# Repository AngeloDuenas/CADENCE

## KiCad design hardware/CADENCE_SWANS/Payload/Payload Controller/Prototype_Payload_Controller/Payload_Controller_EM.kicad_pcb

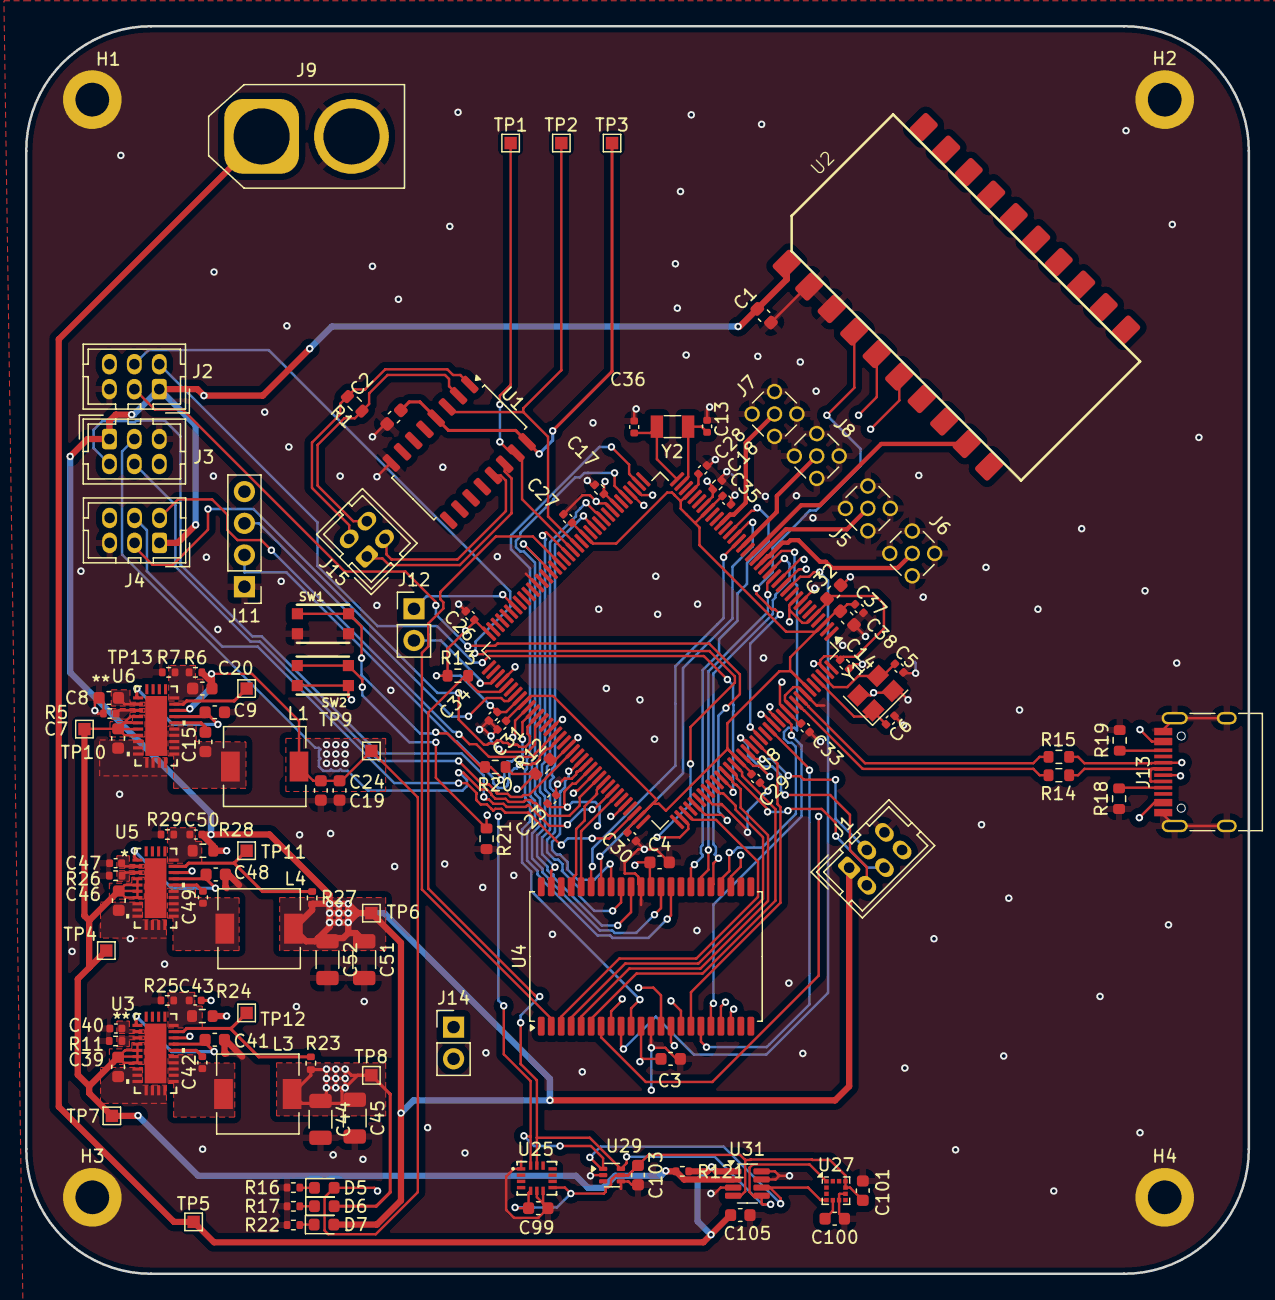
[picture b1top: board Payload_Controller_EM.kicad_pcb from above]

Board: 4 copper layers, 98.0 x 100.0 mm, 126 parts (0 on the bottom side), 110 nets.

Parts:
C1, C2, C3, C4: 10uF; C_0603_1608Metric
C5, C6: 12pF; C_0402_1005Metric
C7, C32, C39, C46: 4.7uF; C_0603_1608Metric
C8: 10nF; C_0603_1608Metric
C9, C38, C41, C48: 1uF; C_0603_1608Metric
C13, C36: 17pF; C_0402_1005Metric
C14, C17, C18: 100nF; R_0402_1005Metric
C15, C101, C103, C105: 100nF; C_0603_1608Metric
C19, C24: 47uF; C_0603_1608Metric
C20: 4.7pF; C_0603_1608Metric
C23, C26, C27, C28, C29, C30, C31, C33, C34, C35, C37, C42, C49: 100nF; C_0402_1005Metric
C40, C47: 10nF; C_0402_1005Metric
C43, C50: 10pF; C_0402_1005Metric
C44, C45, C51, C52: 47uF; C_1206_3216Metric
C99: 10u; C_0603_1608Metric
C100: 220nF; C_0603_1608Metric
D5, D6, D7: RED; LED_0603_1608Metric
H1, H2, H3, H4: MountingHole_Pad_M2.5_2.7mm; MountingHole_2.7mm_M2.5_DIN965_Pad
J1, J2, J3, J4: Conn_01x06_Pin; Hirose_DF11-6DP-2DSA_2x03_P2.00mm_Vertical
J5, J6, J7, J8: Conn_Coaxial; MMCX_Molex_73415-1471_Vertical
J9: Conn_01x02; AMASS_XT60-F_1x02_P7.20mm_Vertical
J11: Conn_01x04; PinHeader_1x04_P2.54mm_Vertical
J12, J14: Conn_01x02; PinHeader_1x02_P2.54mm_Vertical
J13: USB_C_Receptacle_USB2.0_16P; USB_C_Receptacle_HRO_TYPE-C-31-M-12
J15: Conn_02x02_Top_Bottom; Hirose_DF11-4DP-2DSA_2x02_P2.00mm_Vertical
L1: 1.8uH; L_6.3x6.3_H3
L3: 2.5uH; L_6.3x6.3_H3
L4: 10uH; L_6.3x6.3_H3
R1: 120; R_0603_1608Metric
R5, R11: 18.2k; R_0402_1005Metric
R6: 1M; R_0402_1005Metric
R7: 412k; R_0402_1005Metric
R12, R13: 4.7k; R_0603_1608Metric
R14, R15: 22; R_0603_1608Metric
R16, R17, R22: 330; R_0402_1005Metric
R18, R19: 5.1k; R_0603_1608Metric
R20, R21: 10k; R_0603_1608Metric
R23, R27: 100k; R_0402_1005Metric
R24, R28: 1M; R_0603_1608Metric
R25: 243k; R_0402_1005Metric
R26: 41.2k; R_0402_1005Metric
R29: 88.7k; R_0402_1005Metric
R121: 0.002; R_0402_1005Metric
SW1, SW2: KMR2; BTN_KMR2_4.6X2.8
TP1, TP2, TP3, TP4, TP5, TP6, TP7, TP8, TP9, TP10, TP11, TP12, TP13: TestPoint; TestPoint_Pad_1.0x1.0mm
U1: SN65C1168ERGYR; SOP-16_4.55x10.3mm_P1.27mm
U2: RM-VT01-A
U3, U5, U6: LT8612; QFN-28_UDE_LTI
U4: TSOP-II-44_10.16x18.41mm_P0.8mm
U8: ATSAMV71Q21B-A; LQFP-144_20x20mm_P0.5mm
U25: LSM6DSO; LGA-14_L3.0-W2.5-P0.50-TL
U27: LIS2MDL; LGA-12_2x2mm_P0.5mm
U29: TMP112xxDRL; SOT-563
U31: INA219AxDCN; SOT-23-8
Y1: ABM3B-12.000MHZ-B2-T; Crystal_SMD_3225-4Pin_3.2x2.5mm
Y2: ABS07-32.768KHZ-T; Crystal_SMD_3215-2Pin_3.2x1.5mm

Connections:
3V3 Power Good: TP13.1, U6.23 (PG)
5V Power Good: R23.2, TP12.1, U3.23 (PG)
12V Power Good: R27.2, TP11.1, U5.23 (PG)
+1V2: C27.1, C28.1, C29.1, C30.1, C31.1, C35.1, C37.1, C38.1, U8.3 (VDDOUT), U8.29 (VDDCORE), U8.33 (VDDCORE), U8.50 (VDDCORE), U8.81 (VDDCORE), U8.107 (VDDCORE), U8.123 (VDDPLL), U8.139 (VDDUTMIC)
+3.3V: C19.1, C20.2, C24.1, C99.1, C101.1, C103.1, D5.2 (A), L1.2, R6.2, TP9.1, U6.22 (BIAS), U25.5 (VDDIO), U25.8 (VDD), U27.9 (Vdd), U27.10 (Vdd_IO), U29.5 (V+), U31.4 (VS)
+3V3: C3.1, C4.1, C14.1, C17.1, C18.1, C23.1, C26.1, C32.1, C33.1, C34.1, J11.4, J13.A4 (VBUS), J13.A9 (VBUS), J13.B4 (VBUS), J13.B9 (VBUS), J14.2, R12.1, R13.1, R20.1, SW2.A, SW2.A' (P1), U4.11 (VDD), U4.33 (VDD), U8.5 (VDDIN), U8.9 (VREFP), U8.30 (VDDIO), U8.43 (VDDIO), U8.72 (VDDIO), U8.80 (VDDIO), U8.96 (VDDIO), U8.134 (VDDUTMII), U8.143 (VDDPLLUSB)
+5V: C2.1, C43.2, C44.1, C45.1, D6.2 (A), L3.2, R23.1, R24.2, TP3.1, TP8.1, U1.4 (1DE), U1.16 (VCC), U3.22 (BIAS)
+12V: C1.1, C50.2, C51.1, C52.1, D7.2 (A), J1.1, J2.1, J3.1, J4.1, L4.2, R27.1, R28.2, TP6.1, U2.1 (Vdd), U5.22 (BIAS)
/Flight Computer Interface/Payload_RX+: J15.4, R1.1, U1.2 (1A)
/Flight Computer Interface/Payload_RX-: J15.3, R1.2, U1.1 (1B)
/Flight Computer Interface/Payload_TX+: J15.2, U1.13 (1Z)
/Flight Computer Interface/Payload_TX-: J15.1, U1.14 (1Y)
/Instrument/CTRL_EN_0: U2.5 (CTRL_EN), U8.132 (PD1)
/Instrument/CTRL_EN_1: J1.2, U8.126 (PD4)
/Instrument/CTRL_EN_2: J2.2, U8.119 (PD7)
/Instrument/CTRL_EN_3: J3.2, U8.101 (PD10)
/Instrument/CTRL_EN_4: J4.2, U8.88 (PD13)
/Instrument/CTRL_R1_0: U2.6 (CTRL_R1), U8.131 (PD2)
/Instrument/CTRL_R1_1: J1.3, U8.125 (PD5)
/Instrument/CTRL_R1_2: J2.3, U8.113 (PD8)
/Instrument/CTRL_R1_3: J3.3, U8.98 (PD11)
/Instrument/CTRL_R1_4: J4.3, U8.84 (PD14)
/Instrument/CTRL_R2_0: U2.4 (CTRL_R2), U8.128 (PD3)
/Instrument/CTRL_R2_1: J1.4, U8.121 (PD6)
/Instrument/CTRL_R2_2: J2.4, U8.110 (PD9)
/Instrument/CTRL_R2_3: J3.4, U8.92 (PD12)
/Instrument/CTRL_R2_4: J4.4, U8.106 (PD15)
/Instrument/RADFET_OUT0: U2.9 (RADFET_OUT), U8.19 (PC13)
/Instrument/RADFET_OUT1: J5.1 (In), U8.18 (PC15)
/Instrument/RADFET_OUT2: J6.1 (In), U8.17 (PC12)
/Instrument/RADFET_OUT3: J7.1 (In), U8.26 (PB2)
/Instrument/RADFET_OUT4: J8.1 (In), U8.21 (PB0)
/MRAM/A0: U4.3 (A0), U8.111 (PC18)
/MRAM/A1: U4.4 (A1), U8.117 (PC19)
/MRAM/A2: U4.5 (A2), U8.120 (PC20)
/MRAM/A3: U4.6 (A3), U8.122 (PC21)
/MRAM/A4: U4.7 (A4), U8.124 (PC22)
/MRAM/A5: U4.16 (A5), U8.127 (PC23)
/MRAM/A6: U4.17 (A6), U8.130 (PC24)
/MRAM/A7: U4.18 (A7), U8.133 (PC25)
/MRAM/A8: U4.19 (A8), U8.13 (PC26)
/MRAM/A9: U4.20 (A9), U8.12 (PC27)
/MRAM/A10: U4.25 (A10), U8.76 (PC28)
/MRAM/A11: U4.26 (A11), U8.16 (PC29)
/MRAM/A12: U4.27 (A12), U8.15 (PC30)
/MRAM/A13: U4.28 (A13), U8.14 (PC31)
/MRAM/A14: U4.29 (A14), U8.24 (PA18)
/MRAM/A15: U4.38 (A15), U8.23 (PA19)
/MRAM/A16: U4.39 (A16), U8.22 (PA20)
/MRAM/A17: U4.40 (A17), U8.102 (PA0)
/MRAM/A18: U4.41 (A18), U8.99 (PA1)
/MRAM/A19: U4.43 (A19), U8.46 (PA23)
/MRAM/A20: U4.2 (A20), U8.56 (PA24)
/MRAM/MRAM_CTRL.CS: U4.8 (CS), U8.97 (PC14)
/MRAM/MRAM_CTRL.OE: U4.37 (OE), U8.94 (PC11)
/MRAM/MRAM_CTRL.WE: U4.15 (WE), U8.82 (PC8)
/MRAM/MRAM_DATA0: U4.9 (D0), U8.11 (PC0)
/MRAM/MRAM_DATA1: U4.10 (D1), U8.38 (PC1)
/MRAM/MRAM_DATA2: U4.13 (D2), U8.39 (PC2)
/MRAM/MRAM_DATA3: U4.14 (D3), U8.40 (PC3)
/MRAM/MRAM_DATA4: U4.31 (D4), U8.41 (PC4)
/MRAM/MRAM_DATA5: U4.32 (D5), U8.58 (PC5)
/MRAM/MRAM_DATA6: U4.35 (D6), U8.54 (PC6)
/MRAM/MRAM_DATA7: U4.36 (D7), U8.48 (PC7)
/Microcontroller/D+: J13.A6 (D+), J13.B6 (D+), R15.1
/Microcontroller/D-: J13.A7 (D-), J13.B7 (D-), R14.2
/Microcontroller/ERASE: R21.1, SW2.B (S), SW2.B' (S1), U8.87 (PB12)
/Microcontroller/JTAG: J14.1, U8.104 (JTAGSEL)
/Microcontroller/NRST: R20.2, SW1.A, SW1.A' (P1), U8.83 (NRST)
/Microcontroller/SWCLK: J11.2, U8.89 (PB7)
/Microcontroller/SWDIO: J11.3, U8.79 (PB6)
/Microcontroller/URXD0: J12.2, U8.75 (PA9)
/Microcontroller/URXD2: TP2.1, U1.3 (1R), U8.52 (PD25)
/Microcontroller/USB_D+: R15.2, U8.137 (HSDP)
/Microcontroller/USB_D-: R14.1, U8.136 (HSDM)
/Microcontroller/UTXD0: J12.1, U8.66 (PA10)
/Microcontroller/UTXD2: TP1.1, U1.15 (1D), U8.53 (PD26)
/Microcontroller/XIN: C5.2, U8.142 (PB9), Y1.3
/Microcontroller/XIN32: C13.2, U8.35 (PA7), Y2.2
/Microcontroller/XOUT: C6.2, U8.141 (PB8), Y1.1
/Microcontroller/XOUT32: C36.2, U8.36 (PA8), Y2.1
/Peripherals/I2C0_SCL: R13.2, U8.77 (PA4), U25.13 (SCL), U27.1 (SCL/SPC), U29.6 (SDA), U31.5 (SCL)
/Peripherals/I2C0_SDA: R12.2, U8.91 (PA3), U25.14 (SDA), U27.4 (SDA/SDI/SDO), U29.1 (SCL), U31.6 (SDA)
GND: C1.2, C2.2, C3.2, C4.2, C5.1, C6.1, C7.2, C8.1, C9.1, C13.1, C14.2, C17.2, C18.2, C19.2, C23.2, C24.2, C26.2, C27.2, C28.2, C29.2, C30.2, C31.2, C32.2, C33.2, C34.2, C35.2, C36.1, C37.2, C38.2, C39.2, C40.1, C41.1, C44.2, C45.2, C46.2, C47.1, C48.1, C51.2, C52.2, C99.2, C100.2, C101.2, C103.2, C105.2, H1.1 (MP), H2.1 (MP), H3.1 (MP), H4.1 (MP), J1.5, J2.5, J3.5, J4.5, J5.2 (Ext), J6.2 (Ext), J7.2 (Ext), J8.2 (Ext), J9.2, J11.1, J13.A1 (GND), J13.A12 (GND), J13.B1 (GND), J13.B12 (GND), J13.S1 (SHIELD), R5.2, R7.2, R11.2, R16.2, R17.2, R18.1, R19.2, R21.2, R22.2, R25.1, R26.2, R29.1, SW1.B (S), SW1.B' (S1), U1.8 (GND), U2.2 (GND), U2.3 (GND), U3.8 (PGND), U3.9 (PGND), U3.10 (PGND), U3.11 (GND), U3.12 (GND), U3.13 (GND), U3.14 (GND), U4.12 (GND), U4.34 (GND), U5.8 (PGND), U5.9 (PGND), U5.10 (PGND), U5.11 (GND), U5.12 (GND), U5.13 (GND), U5.14 (GND), U6.8 (PGND), U6.9 (PGND), U6.10 (PGND), U6.11 (GND), U6.12 (GND), U6.13 (GND), U6.14 (GND), U8.8 (VREFN), U8.44 (GND), U8.61 (GND), U8.85 (TST), U8.95 (GND), U8.115 (GND), U8.135 (GND), U8.138 (GND), U25.1 (SDO/SA0), U25.6 (GND), U25.7 (GND), U27.6 (GND), U27.8 (GND), U29.2 (GND), U29.4 (ADD0), U31.3 (GND), U31.7 (A0), U31.8 (A1), Y1.2, Y1.4
unnamed: C15.1, L1.1, U6.15 (SW), U6.16 (SW), U6.17 (SW), U6.18 (SW), U6.19 (SW)
unnamed: C42.1, L3.1, U3.15 (SW), U3.16 (SW), U3.17 (SW), U3.18 (SW), U3.19 (SW)
unnamed: C49.1, L4.1, U5.15 (SW), U5.16 (SW), U5.17 (SW), U5.18 (SW), U5.19 (SW)
unnamed: D5.1 (K), R16.1
unnamed: D6.1 (K), R17.1
unnamed: D7.1 (K), R22.1
unnamed: J13.A5 (CC1), R18.2
unnamed: J13.B5 (CC2), R19.1
unnamed: C42.2, U3.20 (BST)
unnamed: C43.1, R24.1, R25.2, U3.24 (FB)
unnamed: C41.2, U3.1 (SYNC), U3.21 (INTVCC)
unnamed: R11.1, U3.3 (RT)
unnamed: C40.2, U3.2 (TR/SS)
unnamed: C49.2, U5.20 (BST)
unnamed: C50.1, R28.1, R29.2, U5.24 (FB)
unnamed: C48.2, U5.1 (SYNC), U5.21 (INTVCC)
unnamed: R26.1, U5.3 (RT)
unnamed: C47.2, U5.2 (TR/SS)
unnamed: C15.2, U6.20 (BST)
unnamed: C20.1, R6.1, R7.1, U6.24 (FB)
unnamed: C9.2, U6.1 (SYNC), U6.21 (INTVCC)
unnamed: R5.1, U6.3 (RT)
unnamed: C8.2, U6.2 (TR/SS)
unnamed: C100.1, U27.5 (C1)
VBAT: C105.1, J9.1, R121.1, TP5.1, U31.1 (IN+)
VBAT_SYS: C7.1, C39.1, C46.1, R121.2, TP4.1, TP7.1, TP10.1, U3.4 (EN/UV), U3.5 (VIN), U3.6 (VIN), U3.7 (VIN), U5.4 (EN/UV), U5.5 (VIN), U5.6 (VIN), U5.7 (VIN), U6.4 (EN/UV), U6.5 (VIN), U6.6 (VIN), U6.7 (VIN), U31.2 (IN-)

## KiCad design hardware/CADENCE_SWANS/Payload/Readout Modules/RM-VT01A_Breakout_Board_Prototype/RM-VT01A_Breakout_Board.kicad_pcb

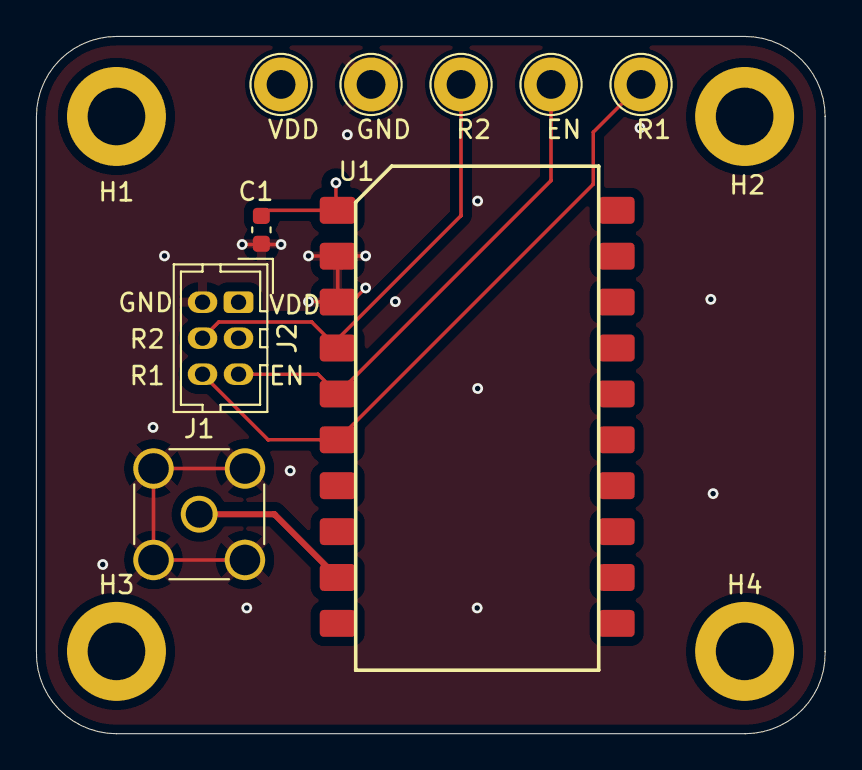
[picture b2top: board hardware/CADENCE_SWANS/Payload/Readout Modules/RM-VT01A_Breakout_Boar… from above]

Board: 4 copper layers, 43.8 x 38.7 mm, 13 parts (0 on the bottom side), 6 nets.

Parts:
C1: 10uF; C_0603_1608Metric
EN: TestPoint; TestPoint_Loop_D2.60mm_Drill1.6mm_Beaded
GND: TestPoint; TestPoint_Loop_D2.60mm_Drill1.6mm_Beaded
H1, H2, H3, H4: MountingHole; MountingHole_3.2mm_M3_ISO14580_Pad
J1: Conn_Coaxial; SMA_Amphenol_132291_Vertical
J2: Conn_01x06; PinHeader_2x03_P2.00mm_Vertical
R1, R2: TestPoint; TestPoint_Loop_D2.60mm_Drill1.6mm_Beaded
U1: RM-VT01-A
VDD: TestPoint; TestPoint_Loop_D2.60mm_Drill1.6mm_Beaded

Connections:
CTRL_EN: EN.1, J2.5, U1.5 (CTRL_EN)
CTRL_R1: J2.6, R1.1, U1.6 (CTRL_R1)
CTRL_R2: J2.4, R2.1, U1.4 (CTRL_R2)
GND: C1.2, GND.1, J1.2 (Ext), J2.2, U1.2 (GND), U1.3 (GND)
unnamed: J1.1 (In), U1.9 (RADFET_OUT)
VDD: C1.1, J2.1, U1.1 (Vdd), VDD.1

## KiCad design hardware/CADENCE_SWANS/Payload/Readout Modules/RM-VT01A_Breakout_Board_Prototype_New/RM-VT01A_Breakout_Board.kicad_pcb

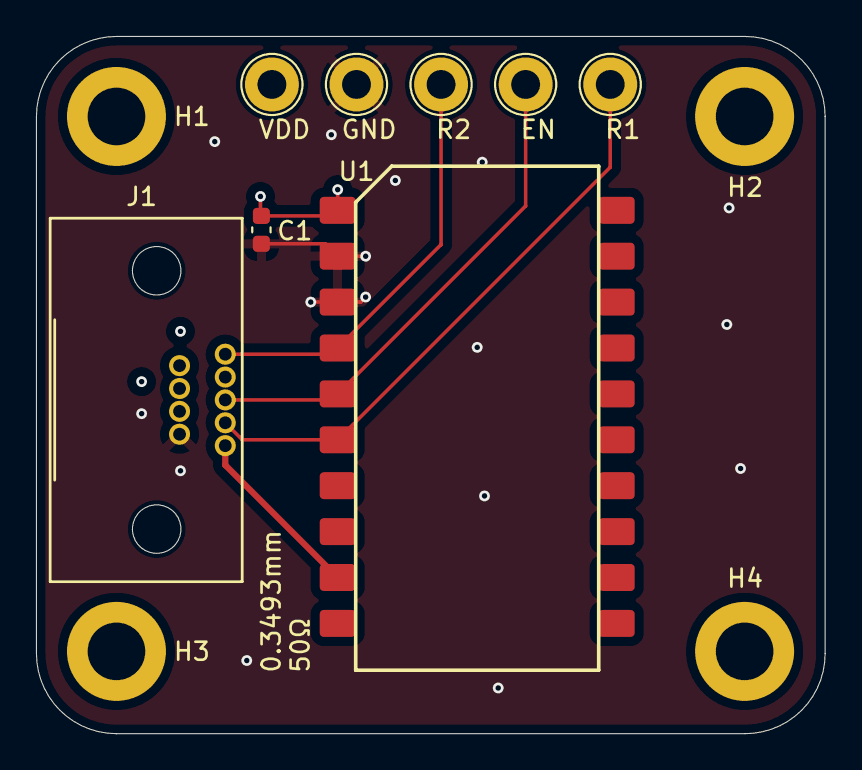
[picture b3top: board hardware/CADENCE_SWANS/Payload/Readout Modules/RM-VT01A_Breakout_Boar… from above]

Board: 4 copper layers, 43.8 x 38.7 mm, 12 parts (0 on the bottom side), 6 nets.

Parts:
C1: 10uF; C_0603_1608Metric
EN: TestPoint; TestPoint_Loop_D2.60mm_Drill1.6mm_Beaded
GND: TestPoint; TestPoint_Loop_D2.60mm_Drill1.6mm_Beaded
H1, H2, H3, H4: MountingHole; MountingHole_3.2mm_M3_ISO14580_Pad
J1: DE9_Pins; CONN_381-009_NRC
R1, R2: TestPoint; TestPoint_Loop_D2.60mm_Drill1.6mm_Beaded
U1: RM-VT01-A
VDD: TestPoint; TestPoint_Loop_D2.60mm_Drill1.6mm_Beaded

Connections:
CONN_COAXIAL: J1.5, U1.9 (RADFET_OUT)
CTRL_EN: EN.1, J1.3, U1.5 (CTRL_EN)
CTRL_R1: J1.4, R1.1, U1.6 (CTRL_R1)
CTRL_R2: J1.1, R2.1, U1.4 (CTRL_R2)
GND: C1.2, GND.1, J1.9, U1.2 (GND), U1.3 (GND)
VDD: C1.1, J1.6, U1.1 (Vdd), VDD.1

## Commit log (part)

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2026-05-01 Layout v2
    added courtyards, grouped components per datasheet specs. unsure of load switch placement. still figuring out ldo 150u cap.
